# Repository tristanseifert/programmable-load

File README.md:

# Programmable Load
A DC programmable load with lots of fun and exciting features, featuring firmware that doesn't suck.

Additional documentation [is available here.](https://wiki.trist.network/books/programmable-load) You can also read about some of the progress on my blog, [starting here.](https://blraaz.me/hardware/2022/04/13/programmable-load-intro.html)

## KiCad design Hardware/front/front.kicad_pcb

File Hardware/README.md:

Here is where the hardware part of the project lives. This consists of a few different boards:

- analog: A 300W load board, based around up to four individual channels, each with their own MOSFET and current sense resistor. Each channel may be individually controlled, and its current individually sensed via a 24-bit ADC. Both the ADC and current drive DAC are connected via a high-speed SPI bus. The board also features a precision 2.5V voltage reference shared by all analog components, as well as a programmable clock generator for the ADC sampling clock.
- controller: Main board, in charge of communicating with external devices (via USB or Ethernet,) driving the user interface, and running the actual control loop for whatever algorithm is desired. It also contains the analog circuitry for sensing input voltage from one of several sources.
- front: Front panel board; features some indicator lights, buttons, and breakout for the display. An [RP2040](https://www.raspberrypi.com/documentation/microcontrollers/rp2040.html) acts as a system controller, driving the LEDs, reading inputs, and talking to the display controller. The board is mounted vertically to front panel of the system.

All of these boards connect to the controller in some way, shape or form. Each board in turn has an EEPROM, which identifies its type, and provides a unique serial number. This is used by the software to figure out what's connected, and what features to offer.

## Front Panels
The `panels` directory contains front and rear panels, designed with [Front Panel Designer](https://www.frontpanelexpress.com/front-panel-designer) and to be manufactured by Front Panel Express. These panels are meant to replace the existing bare aluminum panels that come standard with a [Hammond 1598JBK](https://www.hammfg.com/part/1598JBK) enclosure, for which the boards are designed.

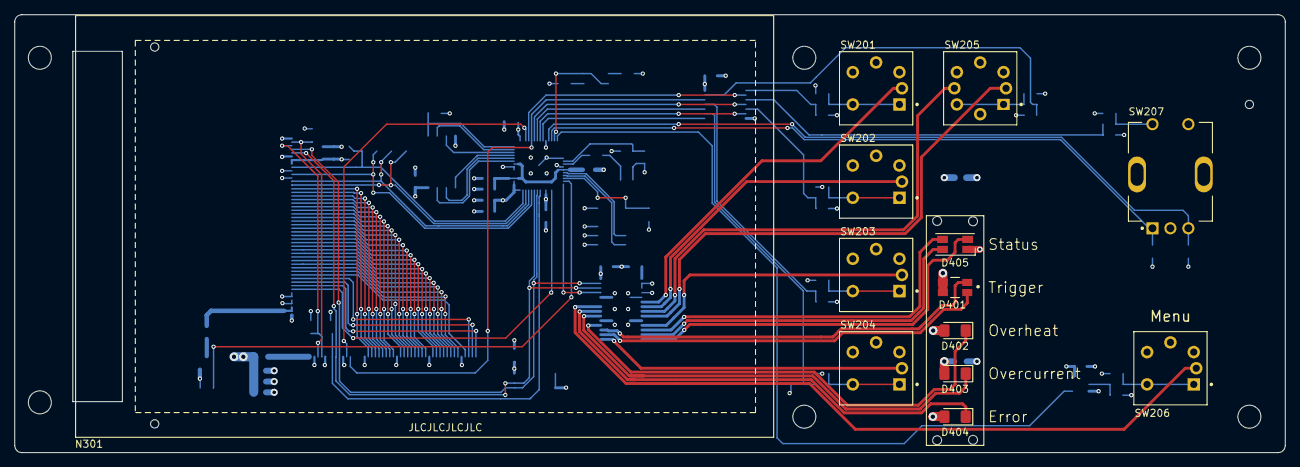
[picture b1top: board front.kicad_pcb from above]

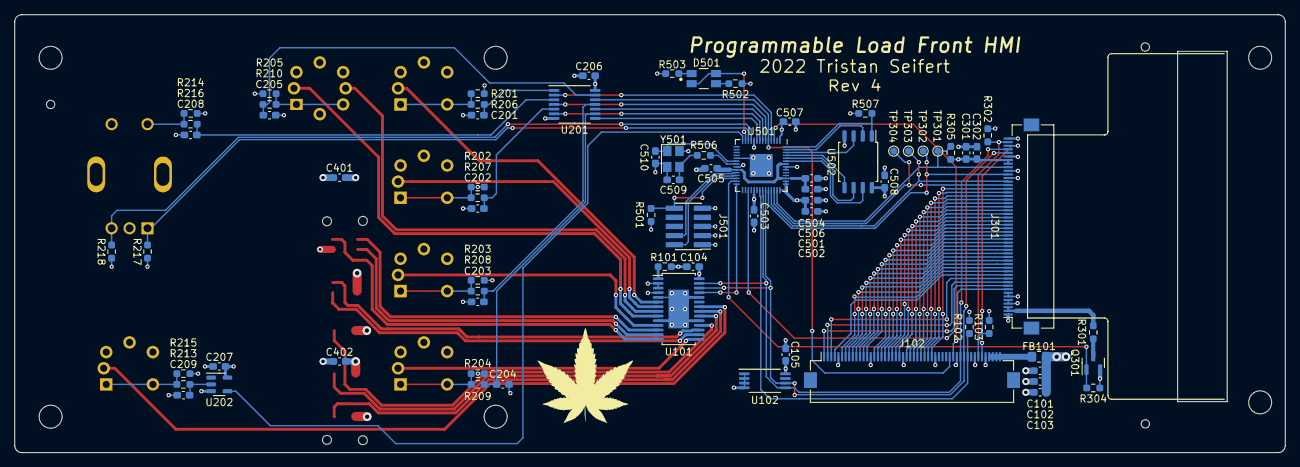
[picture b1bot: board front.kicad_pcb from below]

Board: 4 copper layers, 177.0 x 61.0 mm, 95 parts (73 on the bottom side), 101 nets.

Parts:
C101, C104, C105, C206, C207, C302, C501, C503, C504, C505, C507, C508: 100nF; C_0603_1608Metric_Pad1.08x0.95mm_HandSolder
C102, C103: 22µF; C_0603_1608Metric_Pad1.08x0.95mm_HandSolder
C201, C202, C203, C204, C205, C208, C209, C301, C401, C402, C502, C506: 4.7µF; C_0603_1608Metric_Pad1.08x0.95mm_HandSolder
C509, C510: 22pF; C_0603_1608Metric_Pad1.08x0.95mm_HandSolder
D401, D501: LED_Dual_AAKK; LED-3227
D402, D403: Yellow; LED_1206_3216Metric_Pad1.42x1.75mm_HandSolder
D404: Red; LED_1206_3216Metric_Pad1.42x1.75mm_HandSolder
D405: LED_RGBA; LED_RGB_1210
FB101: FerriteBead_Small; R_0805_2012Metric_Pad1.20x1.40mm_HandSolder
H101, H102, H103, H104, H105, H106: MountingHole; MountingHole_3.2mm_M3
H107, H108, H109: MountingHole; JLCPCB-SmdAssembly-ToolingHole
J102, J301: Conn_02x25_Counter_Clockwise; Hirose_FH12-50S-0.5SH_1x50-1MP_P0.50mm_Horizontal
J501: Conn_ARM_JTAG_SWD_10; PinHeader_2x05_P1.27mm_Vertical_SMD
N301: ER-TFT040-1
Q301: AO3400A; SOT-23
R101: 2k; R_0603_1608Metric_Pad0.98x0.95mm_HandSolder
R102, R103, R201, R202, R203, R204, R205, R214, R215, R217, R218, R302, R304, R305, R501, R507: 10k; R_0603_1608Metric_Pad0.98x0.95mm_HandSolder
R206, R207, R208, R209, R210, R213, R216, R502, R503, R506: 1k; R_0603_1608Metric_Pad0.98x0.95mm_HandSolder
R301: 2R2; R_0603_1608Metric_Pad0.98x0.95mm_HandSolder
SW201, SW202, SW203, SW204: B3W-9002-Y1C; Omron-B3W-90XX-X1X
SW205: B3W-9000-RHG2C; Omron-B3W-90XX-X2X
SW206: B3W-9002-G1G; Omron-B3W-90XX-X1X
SW207: TT EN11; TT_Electronics-EN11-HSM1AF15-0
TP301: /SPI_CS; TestPoint_Pad_D1.0mm
TP302: SPI_SCK; TestPoint_Pad_D1.0mm
TP303: SPI_MOSI; TestPoint_Pad_D1.0mm
TP304: SPI_MISO; TestPoint_Pad_D1.0mm
U101: PCA9955B; HTSSOP-28-1EP_4.4x9.7mm_P0.65mm_EP2.85x5.4mm
U102: AT24CS32-XHM; TSSOP-8_4.4x3mm_P0.65mm
U201: 74LV14; TSSOP-14_4.4x5mm_P0.65mm
U202: 74LVC1G14GV; SOT-23-5
U501: RP2040; QFN-56-1EP_7x7mm_P0.4mm_EP3.2x3.2mm
U502: W25Q128JVS; SOIC-8_5.23x5.23mm_P1.27mm
Y501: 12MHz; Crystal_SMD_3225-4Pin_3.2x2.5mm

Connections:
+1V1: C504.1, C505.1, C506.1, U501.23 (DVDD), U501.45 (VREG_VOUT), U501.50 (DVDD)
+3V3: C101.1, C102.1, C103.1, C104.1, C105.1, C206.1, C207.1, C301.1, C302.1, C401.1, C402.1, C501.1, C502.1, C503.1, C507.1, C508.1, D401.1 (A1), D401.2 (A2), D402.2 (A), D403.2 (A), D404.2 (A), D405.1 (A), FB101.2, J301.1, J301.4, J301.5, J301.39, J301.41, J301.43, J301.44, J501.1 (VTref), R102.2, R103.2, R201.2, R202.2, R203.2, R204.2, R205.2, R214.2, R215.2, R217.1, R218.1, R302.2, R305.2, R501.2, R502.1, R507.2, SW201.A, SW202.A, SW203.A, SW204.A, SW205.A1, SW205.A2, SW206.A, U101.4 (AD2), U101.28 (VCC), U102.8 (VCC), U201.14 (3.3V), U202.5 (VCC), U501.1 (IOVDD), U501.10 (IOVDD), U501.22 (IOVDD), U501.33 (IOVDD), U501.42 (IOVDD), U501.43 (ADC_AVDD), U501.44 (VREG_IN), U501.48 (USB_VDD), U501.49 (IOVDD), U502.8 (VCC)
/B0: J102.31, J301.36
/B1: J102.30, J301.35
/B2: J102.29, J301.34
/B3: J102.28, J301.33
/B4: J102.27, J301.32
/B5: J102.26, J301.31
/B6: J102.25, J301.30
/B7: J102.24, J301.29
/DISP_DE: J102.4, J301.12
/DISP_HSYNC: J102.2, J301.10
/DISP_PCLK: J102.3, J301.11
/DISP_PWM: Q301.1 (G), R304.1, U501.27 (GPIO16)
/DISP_VSYNC: J102.1, J301.9
/ENCODER_A: R217.2, SW207.A, U501.12 (GPIO9)
/ENCODER_B: R218.2, SW207.B, U501.11 (GPIO8)
/Embedded Controller/FLASH_IO0: U501.53 (QSPI_SD0), U502.5 (DI(IO0))
/Embedded Controller/FLASH_IO1: U501.55 (QSPI_SD1), U502.2 (DO(IO1))
/Embedded Controller/FLASH_IO2: U501.54 (QSPI_SD2), U502.3 (IO2)
/Embedded Controller/FLASH_IO3: U501.51 (QSPI_SD3), U502.7 (IO3)
/Embedded Controller/FLASH_SCK: U501.52 (QSPI_SCLK), U502.6 (CLK)
/Embedded Controller/STATUSLED: D501.2 (A2), D501.3 (K1), U501.13 (GPIO10)
/Embedded Controller/SWCLK: J501.4 (SWDCLK/TCK), U501.24 (SWCLK)
/Embedded Controller/SWD: J501.2 (SWDIO/TMS), U501.25 (SWD)
/Embedded Controller/XIN: C510.1, U501.20 (XIN), Y501.1
/Embedded Controller/XOUT: R506.2, U501.21 (XOUT)
/Embedded Controller/~FLASH_CS: R507.1, U501.56 (QSPI_SS), U502.1 (~CS)
/Embedded Controller/~RESET: J501.10 (~RESET), R501.1, U501.26 (RUN)
/G0: J102.22, J301.28
/G1: J102.21, J301.27
/G2: J102.20, J301.26
/G3: J102.19, J301.25
/G4: J102.18, J301.24
/G5: J102.17, J301.23
/G6: J102.16, J301.22
/G7: J102.15, J301.21
/LCD, Backlight driver/LEDK: J301.2, J301.3, R301.1
/LED_EN_G: SW205.K2 (K), U101.8 (LED2)
/LED_EN_R: SW205.K1 (K), U101.9 (LED3)
/LED_ERROR: D404.1 (K), U101.21 (LED13)
/LED_MENU: SW206.K, U101.22 (LED14)
/LED_MODE_CC: SW201.K, U101.6 (LED0)
/LED_MODE_CV: SW202.K, U101.7 (LED1)
/LED_MODE_CW: SW203.K, U101.11 (LED4)
/LED_MODE_EXT: SW204.K, U101.15 (LED8)
/LED_OVRCURR: D403.1 (K), U101.20 (LED12)
/LED_OVRHEAT: D402.1 (K), U101.18 (LED11)
/LED_STATUS_B: D405.4 (BK), U101.13 (LED6)
/LED_STATUS_G: D405.3 (GK), U101.12 (LED5)
/LED_STATUS_R: D405.2 (RK), U101.14 (LED7)
/LED_TRIGGER1: D401.3 (K1), U101.17 (LED10)
/LED_TRIGGER2: D401.4 (K2), U101.16 (LED9)
/R0: J102.13, J301.20
/R1: J102.12, J301.19
/R2: J102.11, J301.18
/R3: J102.10, J301.17
/R4: J102.9, J301.16
/R5: J102.8, J301.15
/R6: J102.7, J301.14
/R7: J102.6, J301.13
/SCL: J102.40, J301.46, U101.26 (SCL), U102.6 (SCL), U501.37 (GPIO25)
/SDA: J102.39, J301.47, U101.27 (SDA), U102.5 (SDA), U501.36 (GPIO24)
/SPI_MISO: J301.37, TP304.1, U501.40 (GPIO28_ADC2)
/SPI_MOSI: J301.38, TP303.1, U501.39 (GPIO27_ADC1)
/SPI_SCK: J301.40, TP302.1, U501.38 (GPIO26_ADC0)
/SW_ENABLE: J102.36, U201.12, U501.5 (GPIO3)
/SW_ENCODER: U201.4, U501.6 (GPIO4)
/SW_MENU: U202.4, U501.14 (GPIO11)
/SW_MODE_CC: U201.2, U501.4 (GPIO2)
/SW_MODE_CV: U201.6, U501.8 (GPIO6)
/SW_MODE_CW: U201.10, U501.7 (GPIO5)
/SW_MODE_EXT: U201.8, U501.9 (GPIO7)
/~DISP_RESET: J301.8, U501.31 (GPIO20)
/~HOST_IRQ: J102.41, R102.1, U501.35 (GPIO23)
/~LED_RESET: U101.25 (~RESET), U501.28 (GPIO17)
/~SPI_CS: J301.42, R305.1, TP301.1, U501.41 (GPIO29_ADC3)
/~SYS_RESET: J102.37, U501.3 (GPIO1)
/~TOUCH_IRQ: J102.44, J301.48, R103.1
/~TOUCH_RESET: J102.45, J301.49, R302.1
GND: C101.2, C102.2, C103.2, C104.2, C105.2, C201.2, C202.2, C203.2, C204.2, C205.2, C206.2, C207.2, C208.2, C209.2, C301.2, C302.2, C401.2, C402.2, C501.2, C502.2, C503.2, C504.2, C505.2, C506.2, C507.2, C508.2, C509.2, C510.2, J102.5, J102.14, J102.23, J102.32, J102.38, J102.43, J102.46, J301.6, J301.7, J301.45, J301.50, J501.3 (GND), J501.5 (GND), J501.9 (GNDDetect), Q301.2 (S), R101.1, R304.2, R503.1, SW201.3, SW201.4, SW202.3, SW202.4, SW203.3, SW203.4, SW204.3, SW204.4, SW205.3, SW205.4, SW206.3, SW206.4, SW207.C, SW207.S2, U101.2 (AD0), U101.3 (AD1), U101.5 (~OE), U101.10 (GND), U101.19 (GND), U101.24 (GND), U101.29 (GND), U102.1 (A0), U102.2 (A1), U102.3 (A2), U102.4 (GND), U201.7 (GND), U202.3 (GND), U501.19 (TESTEN), U501.57 (GND), U502.4 (GND), Y501.2, Y501.4
unnamed: C201.1, R206.2, U201.1
unnamed: C202.1, R207.2, U201.5
unnamed: C203.1, R208.2, U201.11
unnamed: C204.1, R209.2, U201.9
unnamed: C205.1, R210.2, U201.13
unnamed: C208.1, R216.2, U201.3
unnamed: C209.1, R213.1, U202.2
unnamed: C509.1, R506.1, Y501.3
unnamed: D501.1 (A1), R502.2
unnamed: D501.4 (K2), R503.2
unnamed: FB101.1, J102.47, J102.48, J102.49, J102.50
unnamed: Q301.3 (D), R301.2
unnamed: R201.1, R206.1, SW201.1, SW201.2
unnamed: R202.1, R207.1, SW202.1, SW202.2
unnamed: R203.1, R208.1, SW203.1, SW203.2
unnamed: R204.1, R209.1, SW204.1, SW204.2
unnamed: R205.1, R210.1, SW205.1, SW205.2
unnamed: R213.2, R215.1, SW206.1, SW206.2
unnamed: R214.1, R216.1, SW207.S1
unnamed: R101.2, U101.1 (REXT)

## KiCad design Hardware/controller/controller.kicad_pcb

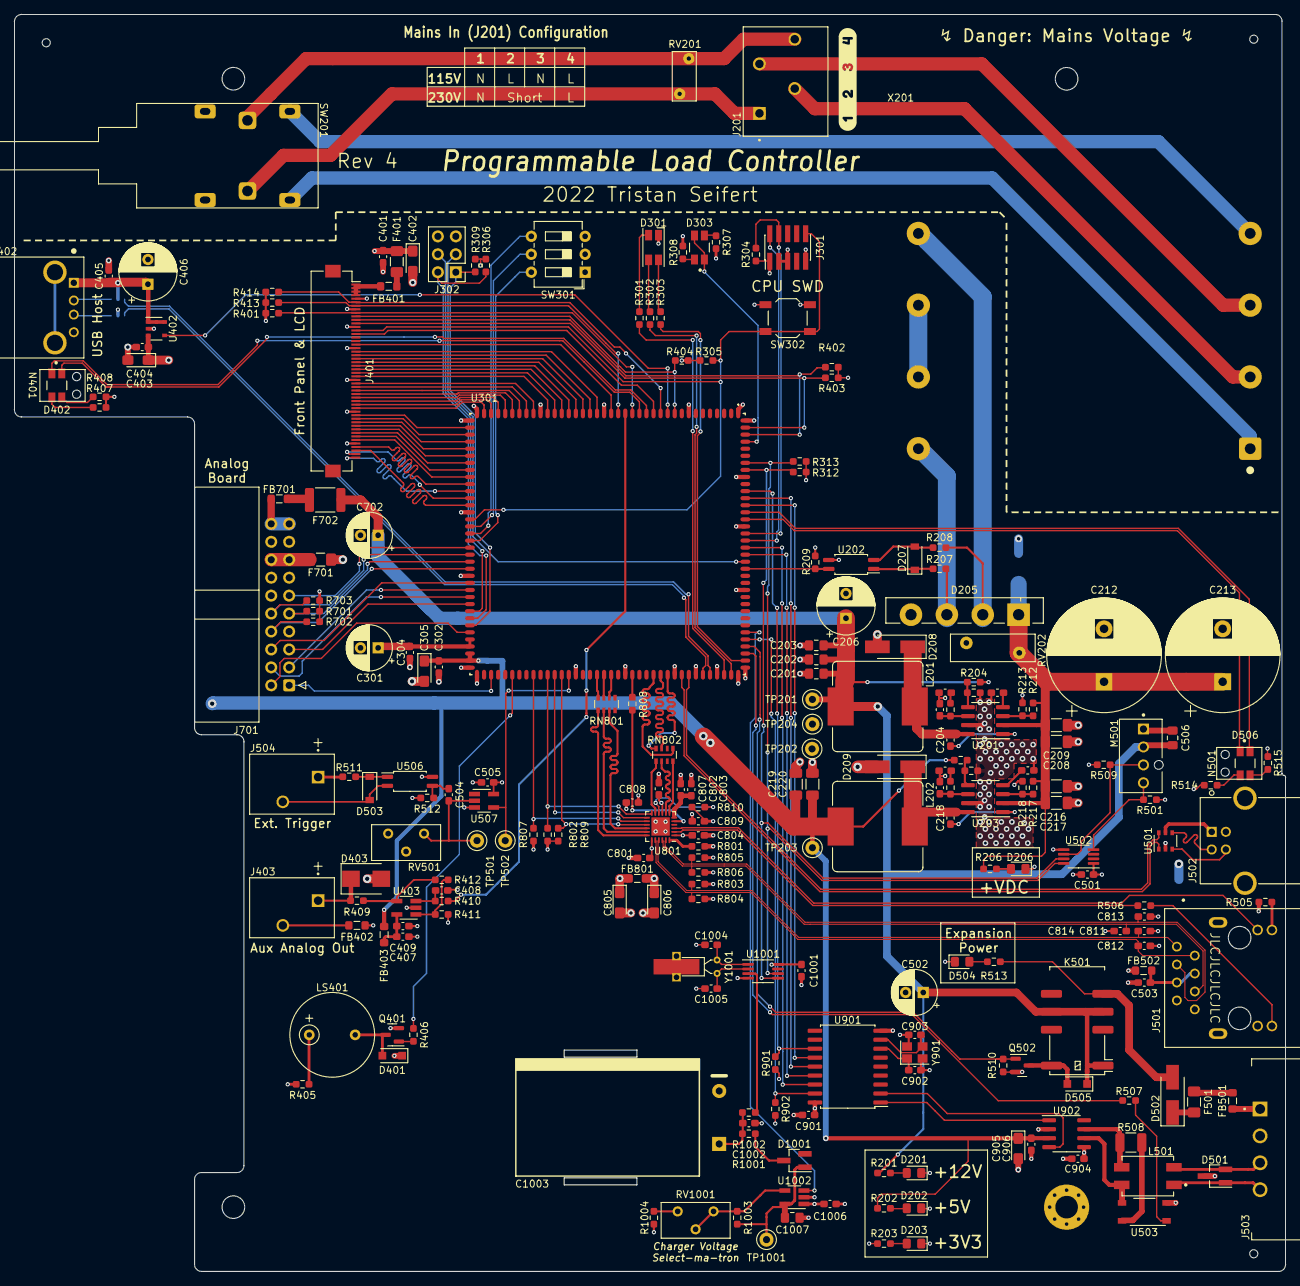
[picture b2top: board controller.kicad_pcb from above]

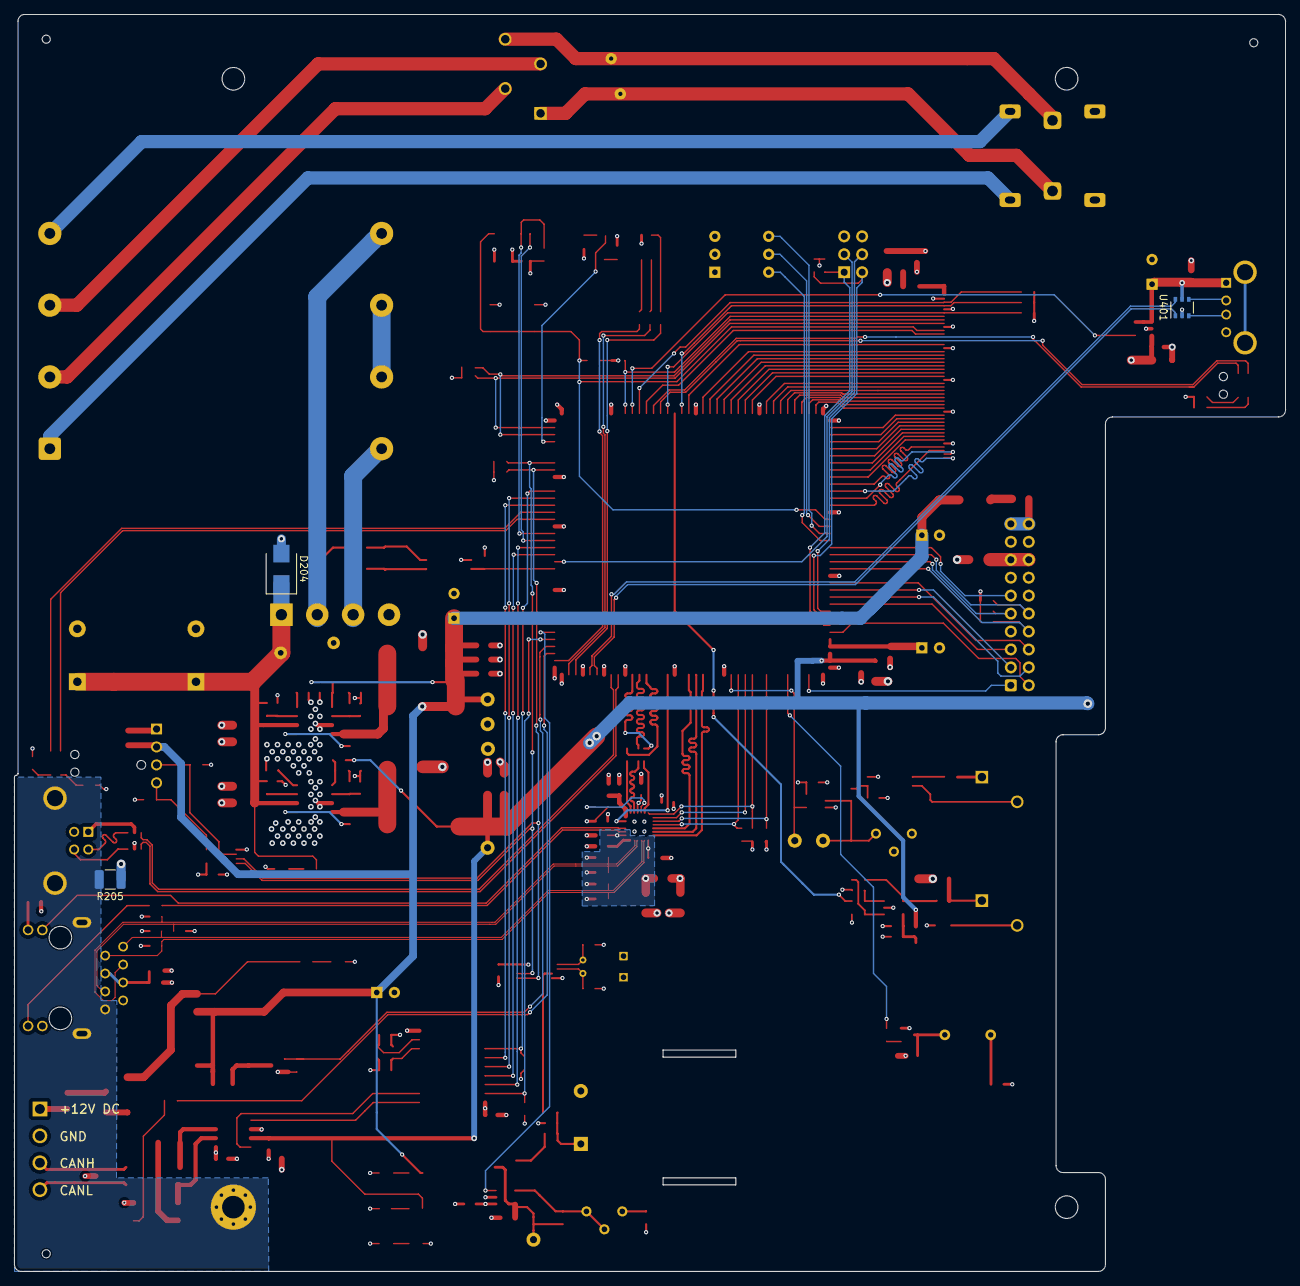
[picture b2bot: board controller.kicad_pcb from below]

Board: 4 copper layers, 180.0 x 178.0 mm, 237 parts (3 on the bottom side), 210 nets.

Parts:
C201, C202, C203, C506, C1007: 10µF; C_0805_2012Metric_Pad1.18x1.45mm_HandSolder
C204, C218, C302, C304, C401, C405, C407, C501, C505, C901, C904, C905, C1001, C1002: 100nF; C_0603_1608Metric_Pad1.08x0.95mm_HandSolder
C205, C215, C801, C804, C807, C808, C809: 10nF; C_0603_1608Metric_Pad1.08x0.95mm_HandSolder
C206, C406: 100µF; CP_Radial_D8.0mm_P3.50mm
C207, C214: 1nF; C_0603_1608Metric_Pad1.08x0.95mm_HandSolder
C208, C209, C216, C217: 10µF; C_1206_3216Metric_Pad1.33x1.80mm_HandSolder
C210, C211: 10pF; C_0603_1608Metric_Pad1.08x0.95mm_HandSolder
C212, C213: 3300µF; CP_Radial_D16.0mm_P7.50mm
C219, C220: 47µF; C_1206_3216Metric_Pad1.33x1.80mm_HandSolder
C301, C502, C702: 47µF; CP_Radial_D6.3mm_P2.50mm
C305, C402, C403, C805, C806, C906: 10µF; CP_EIA-3216-18_Kemet-A_Pad1.58x1.35mm_HandSolder
C404, C409, C504, C803, C1006: 1µF; C_0603_1608Metric_Pad1.08x0.95mm_HandSolder
C408: 330pF; C_0603_1608Metric_Pad1.08x0.95mm_HandSolder
C503: 22nF; C_0603_1608Metric_Pad1.08x0.95mm_HandSolder
C802: 470pF; C_0603_1608Metric_Pad1.08x0.95mm_HandSolder
C811, C812, C813, C814: 22pF; C_0603_1608Metric_Pad1.08x0.95mm_HandSolder
C902, C903: 15pF; C_0603_1608Metric_Pad1.08x0.95mm_HandSolder
C1003: 20F; CP_16x25mm_horiz-L
C1004, C1005: 6.8pF; C_0603_1608Metric_Pad1.08x0.95mm_HandSolder
D201, D202, D203, D206, D504: Green; LED_0805_2012Metric_Pad1.15x1.40mm_HandSolder
D204: 824521241; D_SMB
D205: GBU4M; Diode_Bridge_Vishay_GBU
D207, D503: 1N4148W; D_SOD-123
D208, D209: SS54; D_SMA_Handsoldering
D301: LED_RGBA; LED_RGB_1210
D303, D402, D506: LED_Dual_AAKK; LED-3227
D401, D505: SM4007; D_SOD-123F
D403: SM6T6V8A; D_SMB
D501: ESDONCAN1; SOT-23_Handsoldering
D502: SS14; D_SMA_Handsoldering
D1001: BAS40HE3; SOT-23_Handsoldering
F401, F501, F701: 500mA; Fuse_1206_3216Metric_Pad1.42x1.75mm_HandSolder
F702: 1.6A; Fuse_1812_4532Metric_Pad1.30x3.40mm_HandSolder
FB401, FB402, FB403, FB501, FB502, FB701, FB801: FerriteBead_Small; L_0805_2012Metric_Pad1.05x1.20mm_HandSolder
H101, H102, H104: MountingHole; MountingHole_3.2mm_M3
H103: MountingHole; MountingHole_3.2mm_M3_Pad_Via
H105, H106, H107: MountingHole; JLCPCB-SmdAssembly-ToolingHole
J201: Conn_01x04; CUI_TBL002A-350-04GR-2OR
J301: Conn_ARM_JTAG_SWD_10; PinHeader_2x05_P1.27mm_Vertical_SMD
J302: Conn_02x03_Odd_Even; PinHeader_2x03_P2.54mm_Vertical
J401: Conn_02x25_Counter_Clockwise; Hirose_FH12-50S-0.5SH_1x50-1MP_P0.50mm_Horizontal
J402: USB_A; CUI_UJ2-AH-4-TH
J403, J504: Screw_Terminal_01x02; CUI_TBL002A-350-02GR-2OR
J501: ARJM11C7-009-AB; Abracon-ARJM11C7
J502: USB_B; CUI_UJ2-BH-2-TH
J503: TBP02R1W-381-04BE; CUI_TBP02R1W-381-04BE
J701: Conn_02x10_Odd_Even; IDC-Header_2x10_P2.54mm_Horizontal
K501: EE2-12NU; Relay_DPDT_Kemet_EE2_NU
L201: 18µH; L_Bourns_SRR1280_HandSolder
L202: 10µH; L_Bourns_SRR1280_HandSolder
L501: DR331-513BE; Bourns-DR331-0-0-MFG
LS401: Speaker; PUI-AT-1224-TWT
M501: Fan_4pin; Molex-47053-1000-MFG
N401, N501: SLP3-150-300-F; Lightpipe-SLP3-150-NNN-F
Q401, Q502: MMBT3904; SOT-23
R201, R207, R208, R513: 7k5; R_0603_1608Metric_Pad0.98x0.95mm_HandSolder
R202, R209, R510: 4k7; R_0603_1608Metric_Pad0.98x0.95mm_HandSolder
R203, R301, R302, R303, R312, R313, R402, R403, R701, R702, R802, R807: 2k2; R_0603_1608Metric_Pad0.98x0.95mm_HandSolder
R204, R215: 10k2; R_0603_1608Metric_Pad0.98x0.95mm_HandSolder
R205: 0R; R_1210_3225Metric_Pad1.30x2.65mm_HandSolder
R206, R305, R306, R309, R401, R404, R413, R414, R501, R509, R703, R809, R810, R901, R902, R1003: 10k; R_0603_1608Metric_Pad0.98x0.95mm_HandSolder
R210: 732R; R_0603_1608Metric_Pad0.98x0.95mm_HandSolder
R211: 36k5; R_0603_1608Metric_Pad0.98x0.95mm_HandSolder
R212, R217: 200k; R_0603_1608Metric_Pad0.98x0.95mm_HandSolder
R213, R218: 20k; R_0603_1608Metric_Pad0.98x0.95mm_HandSolder
R214: 68k1; R_0603_1608Metric_Pad0.98x0.95mm_HandSolder
R216: 1k96; R_0603_1608Metric_Pad0.98x0.95mm_HandSolder
R304, R307, R308, R407, R408, R410, R411, R507, R514, R515: 1k; R_0603_1608Metric_Pad0.98x0.95mm_HandSolder
R405, R511: 200R; R_0603_1608Metric_Pad0.98x0.95mm_HandSolder
R406, R409, R505, R506, R1001, R1002: 330R; R_0603_1608Metric_Pad0.98x0.95mm_HandSolder
R412: 620R; R_0603_1608Metric_Pad0.98x0.95mm_HandSolder
R508: 100R; R_1210_3225Metric_Pad1.30x2.65mm_HandSolder
R512: 47k; R_0603_1608Metric_Pad0.98x0.95mm_HandSolder
R801: 12k1 1%; R_0603_1608Metric_Pad0.98x0.95mm_HandSolder
R803, R804, R805, R806: 49R9; R_0603_1608Metric_Pad0.98x0.95mm_HandSolder
R808: 33R; R_0603_1608Metric_Pad0.98x0.95mm_HandSolder
R1004: 3k3; R_0603_1608Metric_Pad0.98x0.95mm_HandSolder
RN801, RN802: 33R; R_Array_Convex_4x0603
RV201: Varistor; RV_Disc_D7mm_W3.4mm_P5mm
RV202: 470KD10; RV_Disc_D12mm_W3.9mm_P7.5mm
RV501: 500k; Potentiometer_Nidec_Copal_CT94EY
RV1001: 10k; Potentiometer_Nidec_Copal_CT94EY
SW201: NE1838EE
SW301: SW_DIP_x03; SW_DIP_SPSTx03_Slide_6.7x9.18mm_W7.62mm_P2.54mm_LowProfile
SW302: SW_MEC_5E; SW_SPST_TL3342
TP201: +12V; TestPoint_Keystone_5000-5004_Miniature
TP202: +3V3; TestPoint_Keystone_5000-5004_Miniature
TP203: +5V; TestPoint_Keystone_5000-5004_Miniature
TP204: GND; TestPoint_Keystone_5000-5004_Miniature
TP501, TP502: Trigger; TestPoint_Keystone_5000-5004_Miniature
TP1001: VBATT; TestPoint_Keystone_5000-5004_Miniature
U201, U203: TPS54331DR; SOIC-8_3.9x4.9mm_P1.27mm
U202, U506: FODM217B; SOP-4_4.4x2.6mm_P1.27mm
U301: MYC-YA151C-4E512D-65-C-T; MYCYA151C4E512D65CT
U401, U501: IP4234CZ6-ALT; TSOP-6_1.65x3.05mm_P0.95mm
U402: AP22817AKB; TSOP-5_1.65x3.05mm_P0.95mm
U403: LMV321; SOT-23-5_HandSoldering
U502: EMC2101-R; MSOP-8_3x3mm_P0.65mm
U503: TLP170A; MFSOP6-4_4.4x3.6mm_P1.27mm
U507: 74LVC1G17; SOT-23-5_HandSoldering
U801: LAN8720A; QFN-24-1EP_4x4mm_P0.5mm_EP2.6x2.6mm
U901: MCP2515-xSO; SOIC-18W_7.5x11.6mm_P1.27mm
U902: MCP2542WFD; SOIC-8_3.9x4.9mm_P1.27mm
U1001: MCP79401; MSOP-8_3x3mm_P0.65mm
U1002: AP2202K-ADJ; SOT-23-5_HandSoldering
X201: FS20-1800-C2; Triad-FS16-2250-C2
Y901: 16MHz; Crystal_SMD_3225-4Pin_3.2x2.5mm
Y1001: 32.768 kHz; Crystal_C26-LF_D2.1mm_L6.5mm_Horizontal_1EP_style2
kibuzzard-62915F53: G***; kibuzzard-62915F53

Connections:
+3V3: C301.1, C304.1, C401.2, C402.1, C501.2, C505.2, C805.1, C807.1, C808.1, C809.1, C901.1, C904.1, C1001.1, C1006.1, D301.1 (A), D401.1 (K), F401.1, F701.1, FB502.1, FB801.1, J301.1 (VTref), J302.6, J501.9 (RLED+), R203.1, R209.1, R304.2, R305.2, R306.2, R307.1, R309.2, R312.2, R313.2, R401.2, R402.2, R403.2, R404.2, R405.2, R407.1, R408.1, R413.2, R414.2, R501.2, R509.1, R514.1, R515.1, R701.2, R702.2, R703.2, R802.1, R807.1, R809.2, R810.1, R901.2, R902.2, SW301.1, SW301.2, SW301.3, TP202.1, U301.70 (V_{BAT}), U301.71 (3V3_{OUT}), U502.1 (VCC), U506.4, U507.5 (VCC), U801.9 (VDDIO), U901.18 (VDD), U902.5 (VIO), U1001.8 (VCC), U1002.1 (V_{In})
+3V3A: C801.1, C804.1, C806.1, FB801.2, R803.1, R804.1, R805.1, R806.1, U801.1 (VDD2A), U801.19 (VDD1A)
+5V: C219.1, C220.1, C302.1, C305.1, C403.1, C404.1, C905.1, C906.1, FB403.2, L202.2, R202.1, R215.1, TP203.1, U301.72 (VDD_{5V}), U301.73 (VDD_{5V}), U402.3 (IN), U902.3 (VCC)
+12V: C201.1, C202.1, C203.1, C206.1, C502.1, C506.1, C702.1, D505.1 (K), F702.2, K501.1, K501.4, K501.9, L201.2, M501.2 (+), R201.1, R204.1, TP201.1
+BATT: R1002.2, U1001.3 (VBAT)
/ANALOG_OUT0: R410.1, U301.17 (PA4)
/ANA_MISO: J701.3, U301.63 (PH7)
/ANA_MOSI: J701.6, U301.62 (PF11)
/ANA_SCK: J701.5, U301.65 (PH6)
/ANA_SCL: J701.9, R701.1, U301.59 (PF14)
/ANA_SDA: J701.8, R702.1, U301.60 (PF15)
/ANA_SEL0: J701.4, U301.64 (PH5)
/ANA_SEL1: J701.2, U301.69 (PA12)
/ANA_SEL2: J701.1, U301.77 (PE11)
/BEEPER: R406.1, U301.80 (PA3)
/CANH: L501.3, R508.2, U902.7 (CANH)
/CANL: L501.4, U503.4, U902.6 (CANL)
/CAN_TERM_EN: R507.2, U301.115 (PF7)
/CPU/BOOT0: SW301.4, U301.55 (BOOT0)
/CPU/BOOT1: SW301.5, U301.54 (BOOT1)
/CPU/BOOT2: SW301.6, U301.56 (BOOT2)
/CPU/ETH_CLK: R808.1, U301.97 (PA1/ETH_RCLK)
/CPU/ETH_CRS_DV: RN802.8 (R1.2), U301.102 (PA7/ETH_RCTL)
/CPU/ETH_MDC: U301.86 (PC1/ETH_MDC), U801.13 (MDC)
/CPU/ETH_MDIO: R802.2, U301.85 (PA2/ETH_MDIO), U801.12 (MDIO)
/CPU/ETH_RXD0: RN802.7 (R2.2), U301.101 (PC4/ETH_RD0)
/CPU/ETH_RXD1: RN802.5 (R4.2), U301.100 (PC5/ETH_RD1)
/CPU/ETH_TXD0: RN801.7 (R2.2), U301.93 (PG13/ETH_TD0)
/CPU/ETH_TXD1: RN801.8 (R1.2), U301.92 (PG14/ETH_TD1)
/CPU/ETH_TX_EN: RN801.6 (R3.2), U301.94 (PB11/ETH_TCTL)
/CPU/Ethernet PHY/RXER: R810.2, U801.10 (RXER/PHYAD0)
/CPU/Expansion CAN Controller/CAN_RX: U901.2 (RXCAN), U902.4 (RXD)
/CPU/Expansion CAN Controller/CAN_TX: U901.1 (TXCAN), U902.1 (TXD)
/CPU/Expansion CAN Controller/OSC1: C903.1, U901.8 (OSC1), Y901.3
/CPU/Expansion CAN Controller/OSC2: C902.1, U901.7 (OSC2), Y901.1
/CPU/RTC_CHARGE: U301.118 (PB12), U1002.3 (EN)
/CPU/SPI3_MISO: U301.137 (PC11/MMC1_D3), U901.14 (SI)
/CPU/SPI3_MOSI: U301.129 (PB2), U901.15 (SO)
/CPU/SPI3_SCK: U301.136 (PC10/MMC1_D2), U901.13 (SCK)
/CPU/STATUS_A7: D303.2 (A2), D303.3 (K1), U301.145 (PZ6)
/CPU/STATUS_B: R303.1, U301.114 (PF8)
/CPU/STATUS_G: R302.1, U301.111 (PD13)
/CPU/STATUS_R: R301.1, U301.110 (PG5)
/CPU/SWDCLK: J301.4 (SWDCLK/TCK), R304.1, U301.132 (SWCLK)
/CPU/SWDIO: J301.2 (SWDIO/TMS), U301.131 (SWDIO)
/CPU/TTY1_RX: J302.1, R309.1, U301.68 (PA11)
/CPU/TTY1_TX: J302.3, U301.128 (PG11)
/CPU/TTY2_RX: J302.2, R306.1, U301.67 (PB5)
/CPU/TTY2_TX: J302.4, U301.66 (PB13)
/CPU/~CAN_RESET: R902.1, U301.117 (PF9), U901.17 (~RESET)
/CPU/~ETH_PHY_IRQ: R807.2, U301.83 (PA5), U801.14 (INT/REFCLKO)
/CPU/~ETH_PHY_RESET: R809.1, U301.87 (PC0), U801.15 (RST)
/CPU/~SPI3_CS: U301.130 (PA15), U901.16 (~CS)
/CPU/~SPI3_IRQ: R901.1, U301.138 (PC12/MMC1_CK), U901.12 (~INT)
/ETH_LED0: J501.11 (LLED+), U801.3 (LED1/REGOFF)
/ETH_RXN: C814.1, J501.6 (RD-), R806.2, U801.22 (RXN)
/ETH_RXP: C813.1, J501.3 (RD+), R805.2, U801.23 (RXP)
/ETH_TXN: C812.2, J501.2 (TD-), R804.2, U801.20 (TXN)
/ETH_TXP: C811.2, J501.1 (TD+), R803.2, U801.21 (TXP)
/EXP_PWR_EN: Q502.1 (B), R510.2, U301.116 (PF6)
/FRONT_SCL: J401.11, R402.1, U301.146 (PH4)
/FRONT_SDA: J401.12, R403.1, U301.147 (PZ7)
/Front Panel Connections/V_{USB}: C405.2, C406.1, J402.1 (VBUS), U401.5 (VBUS), U402.1 (OUT), U402.5 (OUT)
/IO_SCL: R313.1, U301.142 (PZ2), U502.8 (SMCLK), U1001.6 (SCL)
/IO_SDA: R312.1, U301.141 (PZ3), U502.7 (SMDATA), U1001.5 (SDA)
/LCD_B0: J401.20, U301.21 (PD9)
/LCD_B1: J401.21, U301.22 (PG12)
/LCD_B2: J401.22, U301.23 (PG10)
/LCD_B3: J401.23, U301.24 (PD10)
/LCD_B4: J401.24, U301.25 (PI4)
/LCD_B5: J401.25, U301.26 (PI5)
/LCD_B6: J401.26, U301.27 (PI6)
/LCD_B7: J401.27, U301.28 (PI7)
/LCD_DE: J401.47, U301.48 (PE13)
/LCD_G0: J401.29, U301.30 (PE14)
/LCD_G1: J401.30, U301.31 (PE6)
/LCD_G2: J401.31, U301.32 (PH13)
/LCD_G3: J401.32, U301.33 (PH14)
/LCD_G4: J401.33, U301.34 (PH15)
/LCD_G5: J401.34, U301.35 (PI0)
/LCD_G6: J401.35, U301.36 (PI1)
/LCD_G7: J401.36, U301.37 (PI2)
/LCD_HSYNC: J401.49, U301.50 (PI10)
/LCD_PCLK: J401.48, U301.51 (PG7)
/LCD_PWM: J401.18, U301.19 (PB7)
/LCD_R0: J401.38, U301.40 (PH2)
/LCD_R1: J401.39, U301.41 (PH3)
/LCD_R2: J401.40, U301.42 (PH8)
/LCD_R3: J401.41, U301.43 (PH9)
/LCD_R4: J401.42, U301.44 (PH10)
/LCD_R5: J401.43, U301.45 (PH11)
/LCD_R6: J401.44, U301.46 (PH12)
/LCD_R7: J401.45, U301.47 (PE15)
/LCD_VSYNC: J401.50, U301.49 (PI9)
/Power Supply/AC+: D205.3, R207.2, X201.5
/Power Supply/AC-: D205.2, R208.2, X201.8
/Power Supply/ACIN_L: J201.4, RV201.1, SW201.P_{1} (B)
/Power Supply/ACIN_N: J201.1, RV201.2, SW201.P_{2} (B)
/Rear IO Connections/FAN_PWM: M501.4 (PWM), R501.1, U502.4 (FAN)
/Rear IO Connections/FAN_TACH: M501.3 (Tacho), R509.2, U502.6 (TACH)
/TRIGGER: TP502.1, U301.88 (PG8), U507.4
/USBD_DN: U301.105 (USB2N), U501.6
/USBD_DP: U301.104 (USB2P), U501.1
/USBD_LED0: D506.4 (K2), U301.135 (PC9/MMC1_D1)
/USBD_LED1: D506.3 (K1), U301.134 (PC8/MMC1_D0)
/USBH_DN: U301.108 (USB1N), U401.6
/USBH_DP: U301.107 (USB1P), U401.1
/USBH_LED0: D402.4 (K2), U301.14 (PB6)
/USBH_LED1: D402.3 (K1), U301.15 (PB8)
/USBH_PWREN: U301.11 (PE0), U402.4 (EN)
/ZERO_CROSS: R209.2, U202.4, U301.127 (PF10)
/~ANA_IRQ: J701.10, R703.1, U301.58 (PG3)
/~ANA_RESET: J701.11, U301.57 (PD8)
/~ETH_LED1: R506.1, U801.2 (LED2/nINTSEL)
/~FRONT_IRQ: J401.10, R404.1, U301.10 (PC7)
/~FRONT_RESET: J401.9, R401.1, U301.16 (PB9)
/~LOADOFF: J401.15, U301.13 (PE4)
/~SYS_RESET: J301.10 (~RESET), J401.14, R305.1, SW302.1, U301.53 (~RESET)
/~TOUCH_IRQ: J401.7, R413.1, U301.18 (PA6)
/~TOUCH_RESET: J401.6, R414.1, U301.12 (PE1)
GND: C201.2, C202.2, C203.2, C205.2, C206.2, C207.2, C208.2, C209.2, C210.2, C211.2, C212.2, C213.2, C214.2, C215.2, C216.2, C217.2, C219.2, C220.2, C301.2, C302.2, C304.2, C305.2, C401.1, C402.2, C403.2, C404.2, C405.1, C406.2, C407.1, C408.2, C409.2, C501.1, C502.2, C503.1, C505.1, C506.2, C702.2, C801.2, C802.2, C803.2, C804.2, C805.2, C806.2, C807.2, C808.2, C809.2, C811.1, C812.1, C813.2, C814.2, C901.2, C902.2, C903.2, C904.2, C905.2, C906.2, C1001.2, C1002.2, C1003.2, C1004.2, C1005.2, C1006.2, C1007.2, D201.1 (K), D202.1 (K), D203.1 (K), D204.2 (A2), D205.4 (-), D206.1 (K), D208.2 (A), D209.2 (A), D403.2 (A2), D501.3 (common), D504.1 (K), FB402.1, J301.3 (GND), J301.5 (GND), J301.9 (GNDDetect), J302.5, J401.5, J401.8, J401.13, J401.19, J401.28, J401.37, J401.46, J402.4 (GND), J502.4 (GND), J503.2, J701.7, J701.13, J701.14, J701.17, J701.18, M501.1 (-), Q401.2 (E), Q502.2 (E), R205.2, R210.2, R213.2, R216.2, R218.2, R308.1, R411.1, R505.1, R510.1, R512.1, R801.2, R1004.2, RV202.1, RV501.2, RV501.3, SW302.2, TP204.1, U201.7 (GND), U202.3, U203.7 (GND), U301.1 (GND), U301.8 (GND), U301.20 (GND), U301.29 (GND), U301.38 (GND), U301.39 (GND), U301.52 (GND), U301.61 (GND), U301.74 (GND), U301.75 (GND), U301.89 (GND), U301.96 (GND), U301.103 (GND), U301.106 (GND), U301.109 (GND), U301.112 (GND), U301.113 (GND), U301.124 (GND), U301.133 (GND), U301.140 (GND), U301.148 (GND), U401.2 (GND), U402.2 (GND), U403.2 (V-), U501.2 (GND), U502.5 (GND), U503.3, U507.3 (GND), U801.25 (VSS), U901.9 (VSS), U902.2 (GND), U1001.4 (GND), U1002.2 (GND), Y901.2, Y901.4, Y1001.3
GND2: H103.1, J501.8, J501.S1 (SHIELD), J501.S2 (SHIELD), J502.5 (Shield), R205.1
LINE: SW201.R_{1} (C), X201.4
NEUT: SW201.R_{2} (C), X201.1
unnamed: C207.1, R211.2
unnamed: C214.1, R214.2
unnamed: C504.1, RV501.1, TP501.1, U507.2
unnamed: C504.2, R512.2, U506.3
unnamed: C1002.1, C1003.1, R1001.2, R1002.1
unnamed: D201.2 (A), R201.2
unnamed: D202.2 (A), R202.2
unnamed: D203.2 (A), R203.2
unnamed: D206.2 (A), R206.2
unnamed: D207.2 (A), R208.1, U202.2
unnamed: D207.1 (K), R207.1, U202.1
unnamed: C204.2, D208.1 (K), L201.1, U201.8 (PH)
unnamed: C218.2, D209.1 (K), L202.1, U203.8 (PH)
unnamed: D301.4 (BK), R303.2
unnamed: D301.3 (GK), R302.2
unnamed: D301.2 (RK), R301.2
unnamed: D303.1 (A1), R307.2
unnamed: D303.4 (K2), R308.2
unnamed: D401.2 (A), LS401.2, Q401.3 (C)
unnamed: D402.1 (A1), R407.2
unnamed: D402.2 (A2), R408.2
unnamed: D403.1 (A1), J403.1, R409.2
unnamed: D501.1 (A1), J503.4, L501.1
unnamed: D501.2 (A2), J503.3, L501.2
unnamed: D502.2 (A), K501.5, R513.2
unnamed: D502.1 (K), F501.2
unnamed: D503.2 (A), J504.2, U506.2
unnamed: D503.1 (K), R511.1, U506.1
unnamed: D504.2 (A), R513.1
unnamed: D505.2 (A), K501.12, Q502.3 (C)
unnamed: D506.1 (A1), R514.2
unnamed: D506.2 (A2), R515.2
unnamed: D1001.3, R1001.1
unnamed: F401.2, FB401.1
unnamed: F501.1, FB501.2
unnamed: F702.1, FB701.2
unnamed: J201.2, X201.2
unnamed: J201.3, X201.3
unnamed: FB401.2, J401.1, J401.2, J401.3, J401.4
unnamed: J402.3 (D+), U401.3
unnamed: J402.2 (D-), U401.4
unnamed: FB402.2, J403.2
unnamed: C503.2, FB502.2, J501.4 (CT), J501.5 (CT)
unnamed: J501.12 (LLED-), R505.2
unnamed: J501.10 (RLED-), R506.2
unnamed: J502.3 (D+), U501.3
unnamed: J502.2 (D-), U501.4
unnamed: J502.1 (VBUS), U501.5 (VBUS)
unnamed: FB501.1, J503.1
unnamed: J504.1, R511.2
unnamed: F701.2, J701.15, J701.16
unnamed: FB701.1, J701.19, J701.20
unnamed: LS401.1, R405.1
unnamed: Q401.1 (B), R406.2
unnamed: R409.1, R412.2, U403.4
unnamed: R507.1, U503.1
unnamed: R508.1, U503.6
unnamed: R1004.1, RV1001.3
unnamed: RN801.1 (R1.1), U801.18 (TXD1)
unnamed: RN801.2 (R2.1), U801.17 (TXD0)
unnamed: RN801.3 (R3.1), U801.16 (TXEN)
unnamed: RN802.1 (R1.1), U801.11 (CRS_DV/MODE2)
unnamed: RN802.2 (R2.1), U801.8 (RXD0/MODE0)
unnamed: RN802.4 (R4.1), U801.7 (RXD1/MODE1)
unnamed: C204.1, U201.1 (BOOT)
unnamed: C210.1, R211.1, U201.6 (COMP)
unnamed: R212.2, R213.1, U201.3 (EN)
unnamed: C205.1, U201.4 (SS)
unnamed: R204.2, R210.1, U201.5 (V_{Sense})
unnamed: C218.1, U203.1 (BOOT)
unnamed: C211.1, R214.1, U203.6 (COMP)
unnamed: R217.2, R218.1, U203.3 (EN)
unnamed: C215.1, U203.4 (SS)
unnamed: R215.2, R216.1, U203.5 (V_{Sense})
unnamed: R411.2, R412.1, U403.1 (+)
unnamed: C408.1, R410.2, U403.3 (-)
unnamed: C407.2, C409.1, FB403.1, U403.5 (V+)
unnamed: R801.1, U801.24 (RBIAS)
unnamed: C802.1, C803.1, U801.6 (VDDCR)
unnamed: R808.2, U801.5 (XTAL1/CLKIN)
unnamed: C1004.1, U1001.1 (X1), Y1001.1
unnamed: C1005.1, U1001.2 (X2), Y1001.2
unnamed: R1003.2, RV1001.1, RV1001.2, U1002.4 (ADJ)
unnamed: C1007.1, D1001.1, R1003.1, TP1001.1, U1002.5 (V_{Out})
unnamed: X201.6, X201.7
VDC: C208.1, C209.1, C212.1, C213.1, C216.1, C217.1, D204.1 (A1), D205.1 (+), R206.1, R212.1, R217.1, RV202.2, U201.2 (V_{In}), U203.2 (V_{In})
